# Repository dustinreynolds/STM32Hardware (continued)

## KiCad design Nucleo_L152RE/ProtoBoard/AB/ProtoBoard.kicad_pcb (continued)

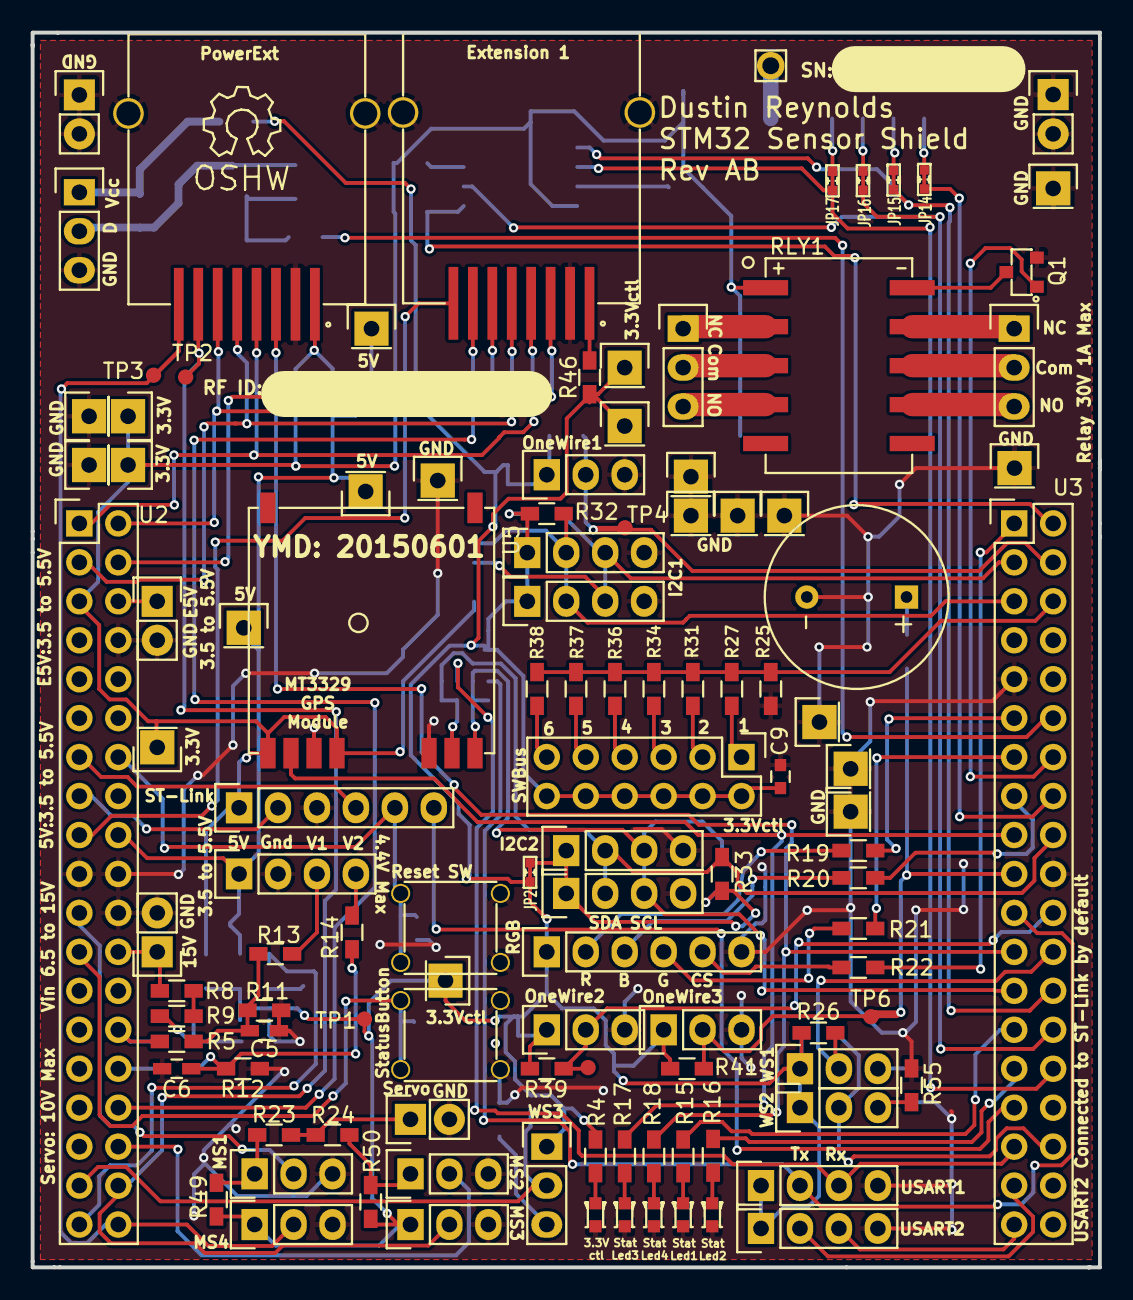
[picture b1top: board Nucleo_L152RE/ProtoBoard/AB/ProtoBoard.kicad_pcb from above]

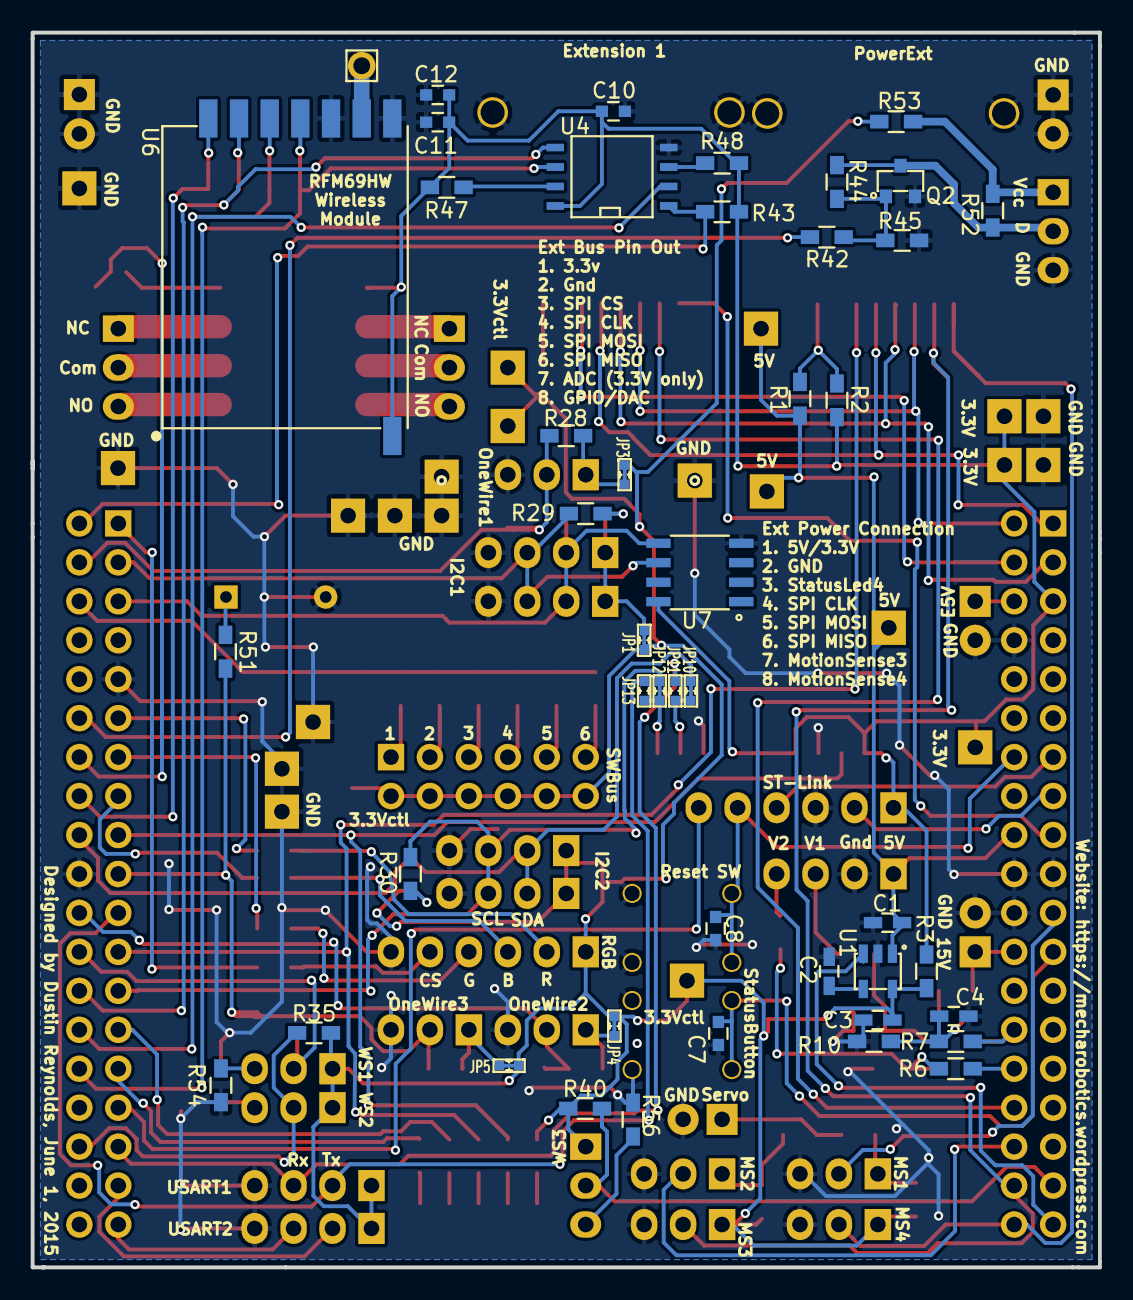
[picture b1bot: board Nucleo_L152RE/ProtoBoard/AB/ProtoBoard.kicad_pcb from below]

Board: 2 copper layers, 69.6 x 80.5 mm, 158 parts (44 on the bottom side), 98 nets.

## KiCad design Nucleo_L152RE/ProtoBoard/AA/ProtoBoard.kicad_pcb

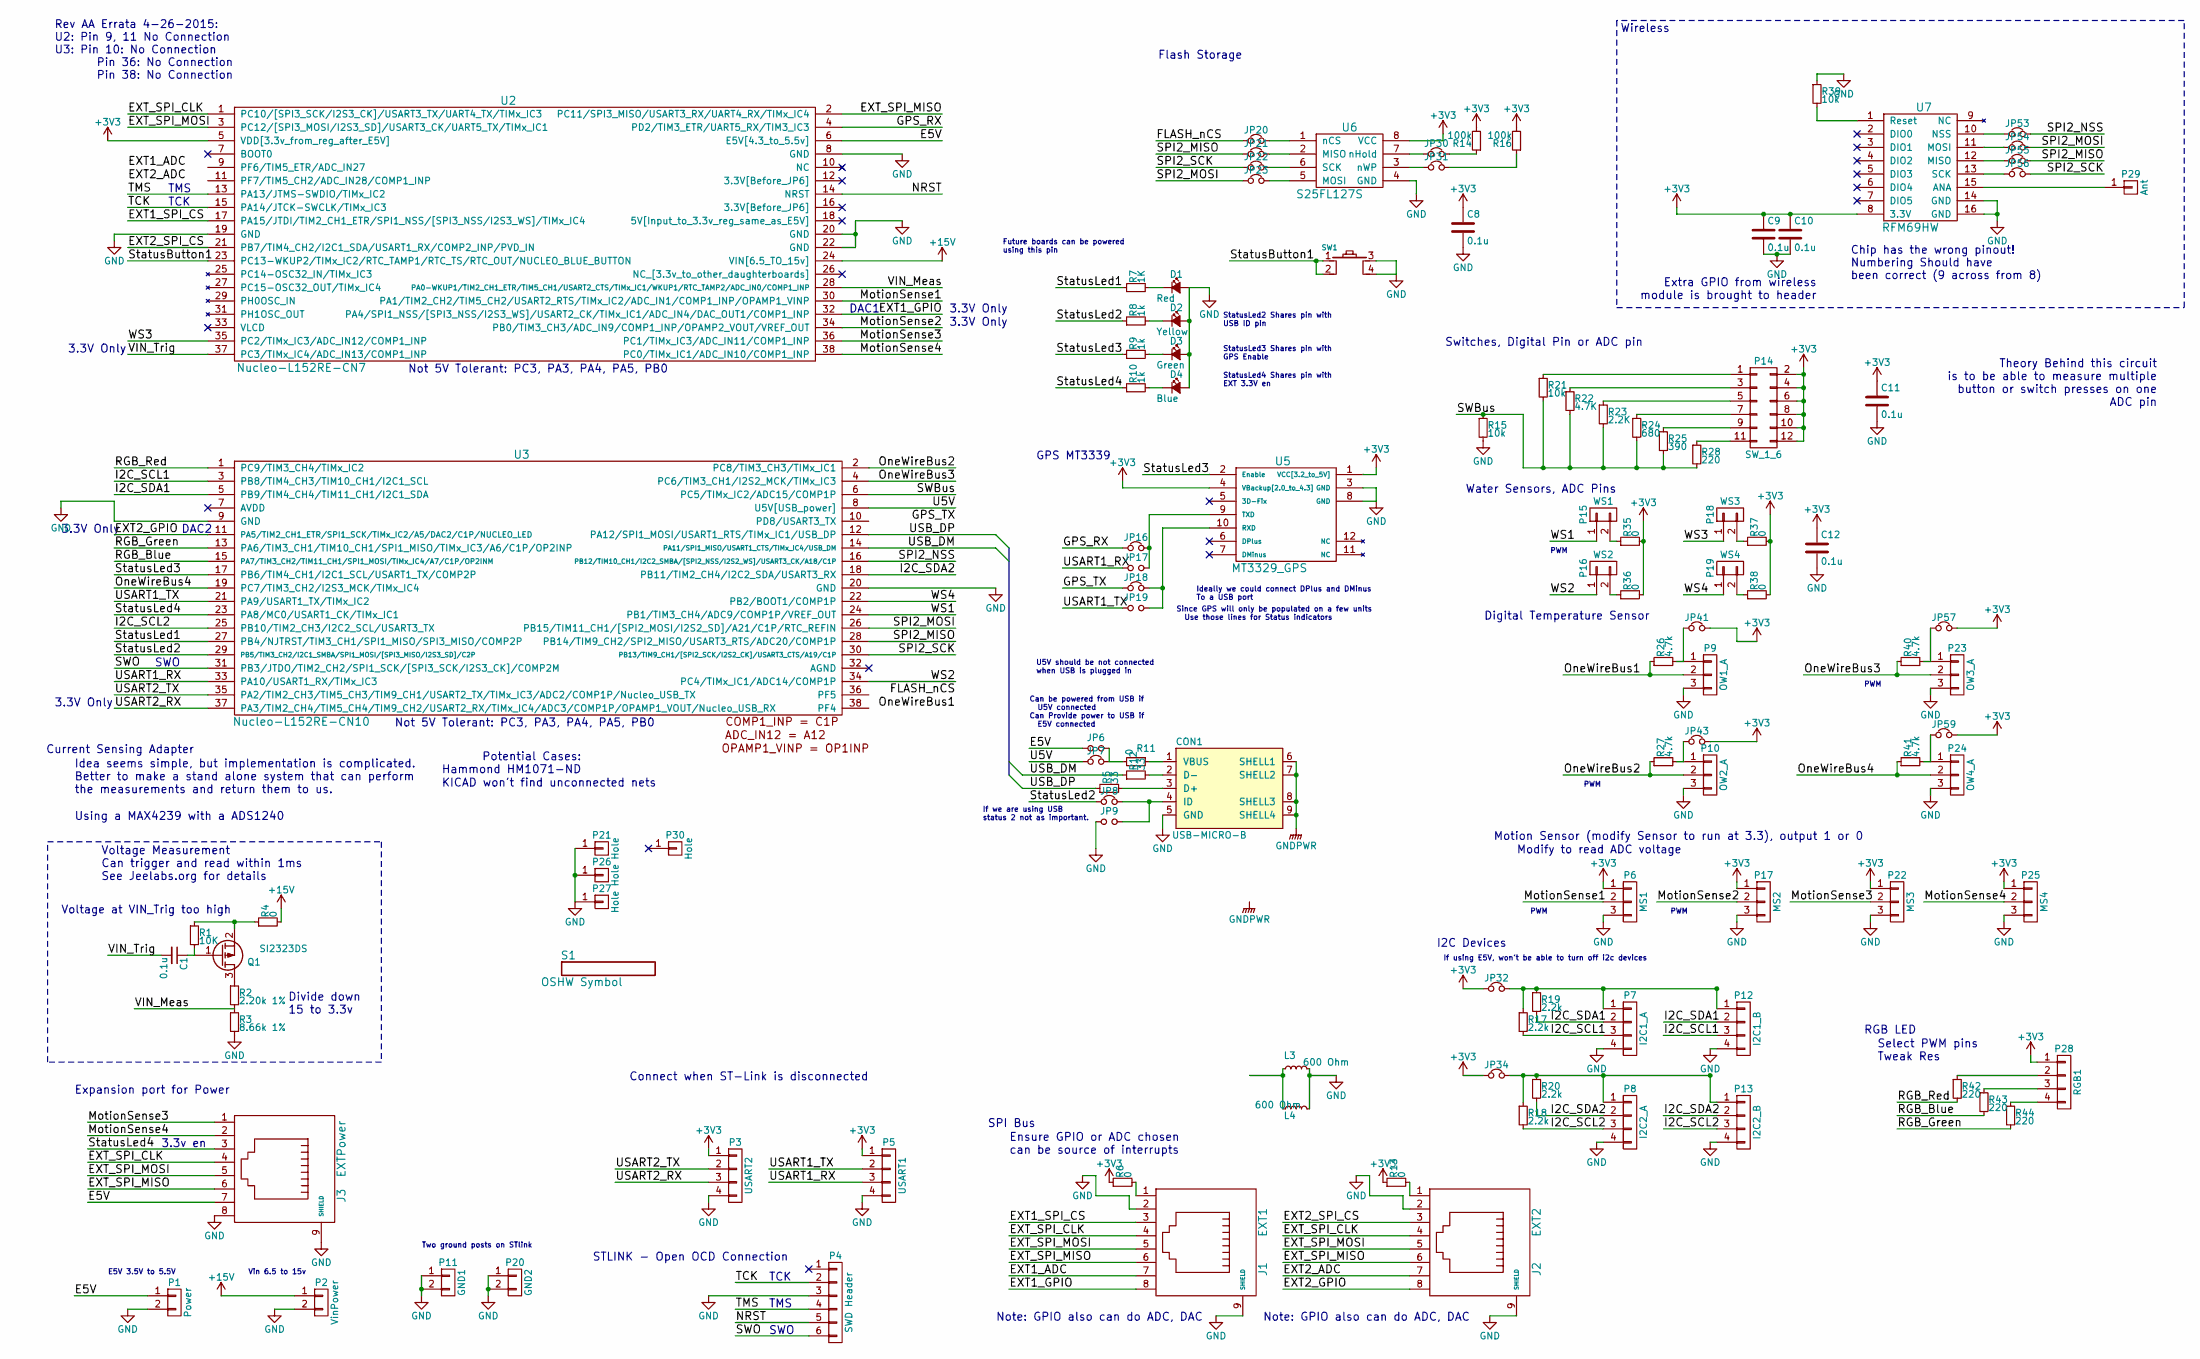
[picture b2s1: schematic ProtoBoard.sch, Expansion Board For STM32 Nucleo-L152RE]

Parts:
C1: 0.1u; C_0603_HandSoldering; Digikey Part Number 490-1532-1-ND
C8, C9, C10, C11, C12: 0.1u; C_0603; Digikey Part Number 490-1532-1-ND
CON1: USB-MICRO-B; USB_micro_AB; Digikey Part Number 609-4053-1-ND
D1: Red; LED_0603; Digikey Part Number 160-1447-1-ND
D2: Yellow; LED_0603; Digikey Part Number 160-1448-1-ND
D3: Green; LED_0603; Digikey Part Number 160-1446-1-ND
D4: Blue; LED_0603; Digikey Part Number 160-1647-1-ND
J1: EXT1; RJ45_SMD; Digikey Part Number RJLSE4238101TTR-ND
J2: EXT2; RJ45_SMD; Digikey Part Number RJLSE4238101TTR-ND
J3: EXTPower; RJ45_SMD; Digikey Part Number RJLSE4238101TTR-ND
JP6, JP9, JP17, JP19: Jumper_NO_Small; SB_NO
JP7, JP8, JP16, JP18, JP20, JP21, JP22, JP23, JP30, JP31, JP32, JP34, JP41, JP43, JP53, JP54, JP55, JP56, JP57, JP59: Jumper_NC_Small; SB_NC
L3, L4: 600 Ohm; R_0603_HandSoldering; Digikey Part Number 240-2371-1-ND
P1: Power; Pin_Header_Straight_1x02
P2: VinPower; Pin_Header_Straight_1x02
P3: USART2; Pin_Header_Straight_1x04
P4: SWD Header; Pin_Header_Straight_1x06
P5: USART1; Pin_Header_Straight_1x04
P6: MS1; Pin_Header_Straight_1x03
P7: I2C1_A; Pin_Header_Straight_1x04
P8: I2C2_A; Pin_Header_Straight_1x04
P9: OW1_A; Pin_Header_Straight_1x03
P10: OW2_A; Pin_Header_Straight_1x03
P11: GND1; Pin_Header_Straight_1x02
P12: I2C1_B; Pin_Header_Straight_1x04
P13: I2C2_B; Pin_Header_Straight_1x04
P14: SW_1_6; Pin_Header_Straight_2x06
P15: WS1; Pin_Header_Straight_1x02
P16: WS2; Pin_Header_Straight_1x02
P17: MS2; Pin_Header_Straight_1x03
P18: WS3; Pin_Header_Straight_1x02
P19: WS4; Pin_Header_Straight_1x02
P20: GND2; Pin_Header_Straight_1x02
P21, P26, P27: Hole; plat_hole_4_20
P22: MS3; Pin_Header_Straight_1x03
P23: OW3_A; Pin_Header_Straight_1x03
P24: OW4_A; Pin_Header_Straight_1x03
P25: MS4; Pin_Header_Straight_1x03
P28: RGB1; Pin_Header_Straight_1x04
P29: Ant; Pin_Header_Straight_1x01
P30: Hole; MountingHole_3mm
Q1: SI2323DS; TO-236; Digikey Part Number SI2323DS-T1-E3CT-ND
R1: 10K; R_0603_HandSoldering; Digikey Part Number P10KGCT-ND
R2: 2.20k 1%; R_0603_HandSoldering; Digikey Part Number P2.20KHCT-ND
R3: 8.66k 1%; R_0603_HandSoldering; Digikey Part Number P8.66KHCT-ND
R4, R6, R13, R35, R36, R37, R38: 0; R_0603_HandSoldering; Digikey Part Number P0.0GCT-ND
R5, R12: 33; R_0603_HandSoldering; Digikey Part Number P33HCT-ND
R7: 1K; R_0603_HandSoldering; Digikey Part Number P1.0KGCT-ND
R8, R9, R10: 1k; R_0603_HandSoldering; Digikey Part Number P1.0KGCT-ND
R11: 0; R_0603_HandSoldering; Digikey Part Number P0.0HCT-ND
R14, R16: 100k; R_0603_HandSoldering; Digikey Part Number RMCF0603FT100KTR-ND
R15, R21, R39: 10k; R_0603_HandSoldering; Digikey Part Number P10KGCT-ND
R17, R18, R19, R20: 2.2k; R_0603_HandSoldering; Digikey Part Number P2.2KGCT-ND
R22: 4.7K; R_0603_HandSoldering; Digikey Part Number P4.7KGCT-ND
R23: 2.2K; R_0603_HandSoldering; Digikey Part Number P2.2KGCT-ND
R24: 680; R_0603_HandSoldering; Digikey Part Number P680GCT-ND
R25: 390; R_0603_HandSoldering; Digikey Part Number P390GCT-ND
R26, R27, R40, R41: 4.7k; R_0603_HandSoldering; Digikey Part Number P4.7KGCT-ND
R28, R42, R43, R44: 220; R_0603_HandSoldering; Digikey Part Number P220GCT-ND
S1: OSHW Symbol; Symbol_OSHW-Logo_SilkScreen
SW1: MomentarySwitch; Tact_switch; Digikey Part Number 450-1650-ND
U2: Nucleo-L152RE-CN7; Pin_Header_Straight_2x19; Digikey Part Number 497-14363-ND
U3: Nucleo-L152RE-CN10; Pin_Header_Straight_2x19
U5: MT3329_GPS; MT3329
U6: S25FL127S; SOIC-8-FLASH; Digikey Part Number 1274-1045-ND
U7: RFM69HW

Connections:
+3V3: C8.1, C9.1, C10.1, C11.1, C12.1, JP32.1, JP34.1, JP41.2, JP43.2, JP57.2, JP59.2, P3.1, P5.1, P6.1, P14.2, P14.4, P14.6, P14.8, P14.10, P14.12, P17.1, P22.1, P25.1, P28.1, R6.1, R13.1, R14.2, R16.2, R35.2, R36.2, R37.2, R38.2, U2.5 (VDD[3.3v_from_reg_after_E5V]), U5.1 (VCC[3.2_to_5V]), U5.4 (VBackup[2.0_to_4.3]), U6.8 (VCC), U7.8 (3.3V)
+15V: P2.1, R4.2, U2.24 (VIN[6.5_TO_15v])
/E5V: J3.7, JP6.1, P1.1, U2.6 (E5V[4.3_to_5.5v])
/EXT1_ADC: J1.7, U2.9 (PF6/TIM5_ETR/ADC_IN27)
/EXT1_GPIO: J1.8, U2.32 (PA4/SPI1_NSS/[SPI3_NSS/I2S3_WS]/USART2_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)
/EXT1_SPI_CS: J1.3, U2.17 (PA15/JTDI/TIM2_CH1_ETR/SPI1_NSS/[SPI3_N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)
/EXT2_ADC: J2.7, U2.11 (PF7/TIM5_CH2/ADC_IN28/COMP1_INP)
/EXT2_GPIO: J2.8, U3.11 (PA5/TIM2_CH1_ETR/SPI1_SCK/TIMx_IC2/A5/D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)
/EXT2_SPI_CS: J2.3, U2.21 (PB7/TIM4_CH2/I2C1_SDA/USART1_RX/COMP2_I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)
/EXT_SPI_CLK: J1.4, J2.4, J3.4, U2.1 (PC10/[SPI3_SCK/I2S3_CK]/USART3_TX/UART4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)
/EXT_SPI_MISO: J1.6, J2.6, J3.6, U2.2 (PC11/SPI3_MISO/USART3_RX/UART4_RX/TIMx_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)
/EXT_SPI_MOSI: J1.5, J2.5, J3.5, U2.3 (PC12/[SPI3_MOSI/I2S3_SD]/USART3_CK/UART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)
/FLASH_nCS: JP20.1, U3.36 (PF5)
/GPS_RX: JP16.1, U2.4 (PD2/TIM3_ETR/UART5_RX/TIM3_IC3)
/GPS_TX: JP18.1, U3.10 (PD8/USART3_TX)
/I2C_SCL1: P7.3, P12.3, R17.2, U3.3 (PB8/TIM4_CH3/TIM10_CH1/I2C1_SCL)
/I2C_SCL2: P8.3, P13.3, R18.2, U3.25 (PB10/TIM2_CH3/I2C2_SCL/USART3_TX)
/I2C_SDA1: P7.2, P12.2, R19.2, U3.5 (PB9/TIM4_CH4/TIM11_CH1/I2C1_SDA)
/I2C_SDA2: P8.2, P13.2, R20.2, U3.18 (PB11/TIM2_CH4/I2C2_SDA/USART3_RX)
/MotionSense1: P6.2, U2.30 (PA1/TIM2_CH2/TIM5_CH2/USART2_RTS/TIMx_I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)
/MotionSense2: P17.2, U2.34 (PB0/TIM3_CH3/ADC_IN9/COMP1_INP/OPAMP2_V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)
/MotionSense3: J3.1, P22.2, U2.36 (PC1/TIMx_IC3/ADC_IN11/COMP1_INP)
/MotionSense4: J3.2, P25.2, U2.38 (PC0/TIMx_IC1/ADC_IN10/COMP1_INP)
/NRST: P4.5, U2.14 (NRST)
/OneWireBus1: P9.2, R26.1, U3.38 (PF4)
/OneWireBus2: P10.2, R27.1, U3.2 (PC8/TIM3_CH3/TIMx_IC1)
/OneWireBus3: P23.2, R40.1, U3.4 (PC6/TIM3_CH1/I2S2_MCK/TIMx_IC3)
/OneWireBus4: P24.2, R41.1, U3.19 (PC7/TIM3_CH2/I2S3_MCK/TIMx_IC4)
/RGB_Blue: R43.2, U3.15 (PA7/TIM3_CH2/TIM11_CH1/SPI1_MOSI/TIMx_I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)
/RGB_Green: R44.2, U3.13 (PA6/TIM3_CH1/TIM10_CH1/SPI1_MISO/TIMx_I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)
/RGB_Red: R42.2, U3.1 (PC9/TIM3_CH4/TIMx_IC2)
/SPI2_MISO: JP21.1, JP55.2, U3.28 (PB14/TIM9_CH2/SPI2_MISO/USART3_RTS/ADC2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)
/SPI2_MOSI: JP23.1, JP54.2, U3.26 (PB15/TIM11_CH1/[SPI2_MOSI/I2S2_SD]/A21/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)
/SPI2_NSS: JP53.2, U3.16 (PB12/TIM10_CH1/I2C2_SMBA/[SPI2_NSS/I2S2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)
/SPI2_SCK: JP22.1, JP56.2, U3.30 (PB13/TIM9_CH1/[SPI2_SCK/I2S2_CK]/USART3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)
/SWBus: R15.1, R21.2, R22.2, R23.2, R24.2, R25.2, R28.2, U3.6 (PC5/TIMx_IC2/ADC15/COMP1P)
/SWO: P4.6, U3.31 (PB3/JTDO/TIM2_CH2/SPI1_SCK/[SPI3_SCK/I2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)
/StatusButton1: SW1.1, SW1.2, U2.23 (PC13-WKUP2/TIMx_IC2/RTC_TAMP1/RTC_TS/RT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)
/StatusLed1: R7.1, U3.27 (PB4/NJTRST/TIM3_CH1/SPI1_MISO/SPI3_MISO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)
/StatusLed2: JP8.1, R8.1, U3.29 (PB5/TIM3_CH2/I2C1_SMBA/SPI1_MOSI/[SPI3_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)
/StatusLed3: R9.1, U3.17 (PB6/TIM4_CH1/I2C1_SCL/USART1_TX/COMP2P), U5.2 (Enable)
/StatusLed4: J3.3, R10.1, U3.23 (PA8/MC0/USART1_CK/TIMx_IC1)
/TCK: P4.2, U2.15 (PA14/JTCK-SWCLK/TIMx_IC3)
/TMS: P4.4, U2.13 (PA13/JTMS-SWDIO/TIMx_IC2)
/U5V: JP7.1, U3.8 (U5V[USB_power])
/USART1_RX: JP17.1, P5.3, U3.33 (PA10/USART1_RX/TIMx_IC3)
/USART1_TX: JP19.1, P5.2, U3.21 (PA9/USART1_TX/TIMx_IC2)
/USART2_RX: P3.3, U3.37 (PA3/TIM2_CH4/TIM5_CH4/TIM9_CH2/USART2_R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)
/USART2_TX: P3.2, U3.35 (PA2/TIM2_CH3/TIM5_CH3/TIM9_CH1/USART2_T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)
/USB_DM: R12.1, U3.14 (PA11/SPI1_MISO/USART1_CTS/TIMx_IC4/USB_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)
/USB_DP: R5.1, U3.12 (PA12/SPI1_MOSI/USART1_RTS/TIMx_IC1/USB_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)
/VIN_Meas: R2.2, R3.1, U2.28 (PA0-WKUP1/TIM2_CH1_ETR/TIM5_CH1/USART2_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)
/VIN_Trig: C1.2, U2.37 (PC3/TIMx_IC4/ADC_IN13/COMP1_INP)
/WS1: P15.1, U3.24 (PB1/TIM3_CH4/ADC9/COMP1P/VREF_OUT)
/WS2: P16.1, U3.34 (PC4/TIMx_IC1/ADC14/COMP1P)
/WS3: P18.1, U2.35 (PC2/TIMx_IC3/ADC_IN12/COMP1_INP)
/WS4: P19.1, U3.22 (PB2/BOOT1/COMP1P)
GND: C8.2, C9.2, C10.2, C11.2, C12.2, CON1.5 (GND), D1.2 (A), D2.2 (A), D3.2 (A), D4.2 (A), J1.2, J1.9 (SHIELD), J2.2, J2.9 (SHIELD), J3.8, J3.9 (SHIELD), JP9.1, L3.2, L4.2, P1.2, P2.2, P3.4, P4.3, P5.4, P6.3, P7.4, P8.4, P9.3, P10.3, P11.1, P11.2, P12.4, P13.4, P17.3, P20.1, P20.2, P21.1, P22.3, P23.3, P24.3, P25.3, P26.1, P27.1, R3.2, R15.2, R39.1, SW1.3, SW1.4, U2.8 (GND), U2.19 (GND), U2.20 (GND), U2.22 (GND), U3.9 (GND), U3.20 (GND), U5.3 (GND), U5.8 (GND), U6.4 (GND), U7.14 (GND), U7.16 (GND)
unnamed: C1.1, Q1.1 (G), R1.2
unnamed: CON1.1 (VBUS), R11.1
unnamed: CON1.2 (D-), R12.2
unnamed: CON1.3 (D+), R5.2
unnamed: CON1.4 (ID), JP8.2, JP9.2
unnamed: D1.1 (K), R7.2
unnamed: D2.1 (K), R8.2
unnamed: D3.1 (K), R9.2
unnamed: D4.1 (K), R10.2
unnamed: J1.1, R6.2
unnamed: J2.1, R13.2
unnamed: JP6.2, JP7.2, R11.2
unnamed: JP16.2, JP17.2, U5.9 (TXD)
unnamed: JP18.2, JP19.2, U5.10 (RXD)
unnamed: JP20.2, U6.1 (nCS)
unnamed: JP21.2, U6.2 (MISO)
unnamed: JP22.2, U6.6 (SCK)
unnamed: JP23.2, U6.5 (MOSI)
unnamed: JP30.1, U6.7 (nHold)
unnamed: JP30.2, R14.1
unnamed: JP31.1, U6.3 (nWP)
unnamed: JP31.2, R16.1
unnamed: JP32.2, P7.1, P12.1, R17.1, R19.1
unnamed: JP34.2, P8.1, P13.1, R18.1, R20.1
unnamed: JP41.1, P9.1, R26.2
unnamed: JP43.1, P10.1, R27.2
unnamed: JP53.1, U7.10 (NSS)
unnamed: JP54.1, U7.11 (MOSI)
unnamed: JP55.1, U7.12 (MISO)
unnamed: JP56.1, U7.13 (SCK)
unnamed: JP57.1, P23.1, R40.2
unnamed: JP59.1, P24.1, R41.2
unnamed: P14.1, R21.1
unnamed: P14.3, R22.1
unnamed: P14.5, R23.1
unnamed: P14.7, R24.1
unnamed: P14.9, R25.1
unnamed: P14.11, R28.1
unnamed: P15.2, R35.1
unnamed: P16.2, R36.1
unnamed: P18.2, R37.1
unnamed: P19.2, R38.1
unnamed: P28.2, R42.1
unnamed: P28.3, R43.1
unnamed: P28.4, R44.1
unnamed: P29.1, U7.15 (ANA)
unnamed: Q1.2 (S), R1.1, R4.1
unnamed: Q1.3 (D), R2.1
unnamed: R39.2, U7.1 (Reset)

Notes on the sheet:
TCK
TMS
SWO
Wireless
Connect when ST-Link is disconnected
Not 5V Tolerant: PC3, PA3, PA4, PA5, PB0
Switches, Digital Pin or ADC pin
Water Sensors, ADC Pins
Digital Temperature Sensor
Motion Sensor (modify Sensor to run at 3.3), output 1 or 0
Current Sensing Adapter
STLINK - Open OCD Connection
Theory Behind this circuit is to be able to measure multiple button or switch presses on one ADC pin
Flash Storage
Idea seems simple, but implementation is complicated. Better to make a stand alone system that can perform the measurements and return them to us.
Using a MAX4239 with a ADS1240
If using E5V, won't be able to turn off i2c devices
Extra GPIO from wireless module is brought to header
Potential Cases: Hammond HM1071-ND
SPI Bus
Ensure GPIO or ADC chosen can be source of interrupts
RGB LED
Select PWM pins Tweak Res
Voltage Measurement Can trigger and read within 1ms See Jeelabs.org for details
Divide down 15 to 3.3v
DAC2
DAC1
Note: GPIO also can do ADC, DAC
U5V should be not connected when USB is plugged in
Ideally we could connect DPlus and DMinus To a USB port
Vin 6.5 to 15v
E5V 3.5V to 5.5V
If we are using USB status 2 not as important.
I2C Devices
StatusLed2 Shares pin with USB ID pin
Can be powered from USB if U5V connected Can Provide power to USB if E5V connected
PWM
GPS MT3339
Future boards can be powered using this pin
Since GPS will only be populated on a few units Use those lines for Status indicators

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
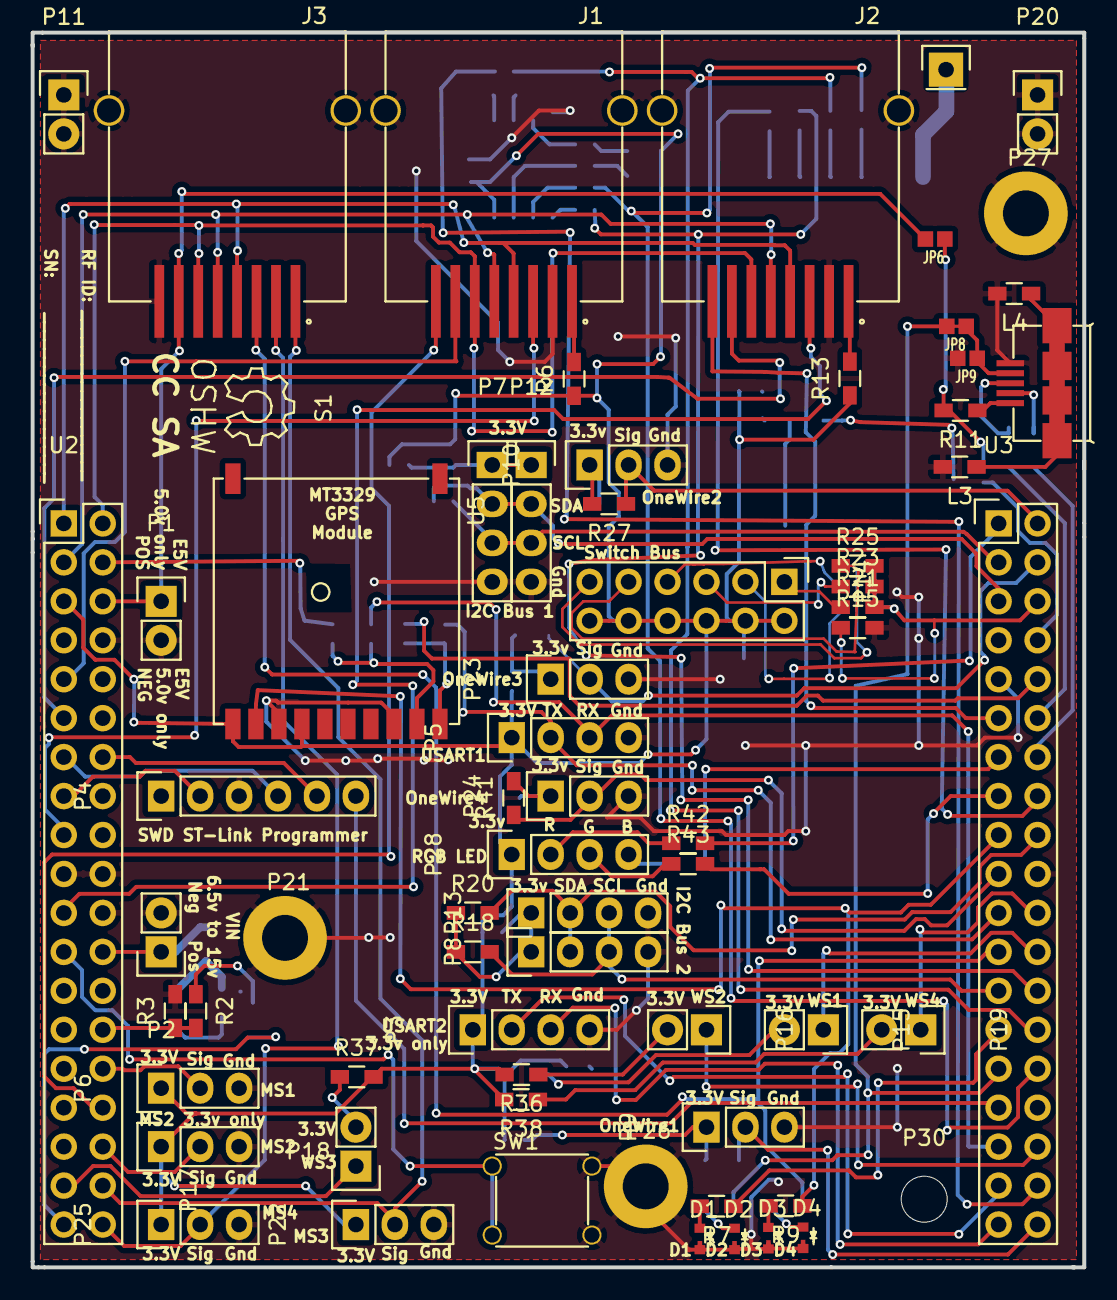
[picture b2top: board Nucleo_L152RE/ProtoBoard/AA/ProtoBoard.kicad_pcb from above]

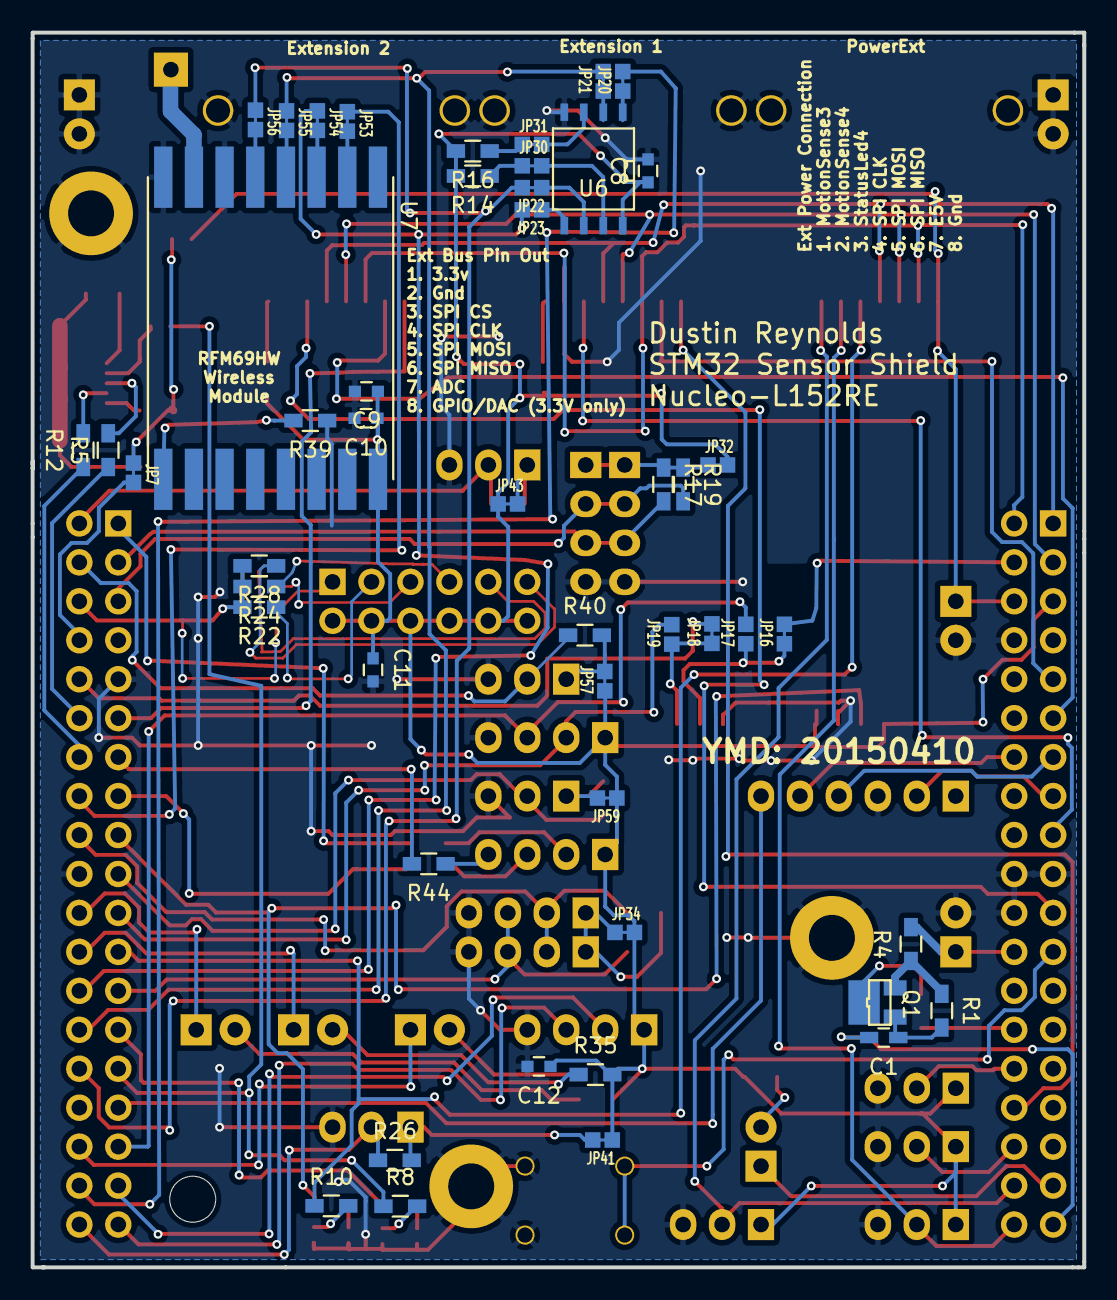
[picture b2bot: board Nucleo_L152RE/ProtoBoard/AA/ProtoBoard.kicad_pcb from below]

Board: 2 copper layers, 68.6 x 80.5 mm, 116 parts (48 on the bottom side), 108 nets.

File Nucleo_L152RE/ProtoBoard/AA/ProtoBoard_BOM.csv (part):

"Source:","C:/Customers/Dustin/SensorNodes/STM32/EE/Nucleo_L152RE/ProtoBoard/AA/ProtoBoard.sch"
"Date:","4/10/2015 3:52:45 PM"
"Tool:","Eeschema (2015-03-26 BZR 5542)-product"
"Generator:","dustin_bom_csv_grouped_by_value_with_fp.py"
"Component Count:","116"
"Ref","Quantity","Value","Cmp name","Footprint","Description","Vendor","Datasheet","Digikey Part Number","Digikey URL","Mouser Part Number","Mouser URL","Ebay","Manufacture Part Number"
"C1, ","1","0.1u","C_Small","Capacitors_SMD:C_0603_HandSoldering","Unpolarized capacitor","","http://www.digikey.com/product-detail/en/GRM188R71C104KA01D/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","490-1532-1-ND","","","","","GRM188R71C104KA01D"
"C10, C9, C8, C11, C12, ","5","0.1u","C","Capacitors_SMD:C_0603","Unpolarized capacitor","","","490-1532-1-ND","","","","","GRM188R71C104KA01D"
"CON1, ","1","USB-MICRO-B","USB-MICRO-B","nucleo:USB_micro_AB","USB Mini B connector","","http://www.digikey.com/product-detail/en/10104111-0001LF/609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","609-4053-1-ND","http://www.digikey.com/product-detail/en/10104111-0001LF/609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","","","","10104111-0001LF"
"D1, ","1","Red","Led_Small","nucleo:LED_0603","Led","","http://optoelectronics.liteon.com/upload/download/DS22-2000-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","160-1447-1-ND","http://www.digikey.com/product-detail/en/LTST-C191KRKT/160-1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","","","","LTST-C191KRKT"
"D2, ","1","Yellow","Led_Small","nucleo:LED_0603","Led","","http://optoelectronics.liteon.com/upload/download/DS22-2000-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","160-1448-1-ND","http://www.digikey.com/product-detail/en/LTST-C191KSKT/160-1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","","","","LTST-C191KSKT"
"D3, ","1","Green","Led_Small","nucleo:LED_0603","Led","","http://optoelectronics.liteon.com/upload/download/DS22-2000-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","160-1446-1-ND","http://www.digikey.com/product-detail/en/LTST-C191KGKT/160-1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","","","","LTST-C191KGKT"
"D4, ","1","Blue","Led_Small","nucleo:LED_0603","Led","","http://optoelectronics.liteon.com/upload/download/DS22-2000-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","160-1647-1-ND","http://www.digikey.com/product-detail/en/LTST-C191TBKT/160-1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","","","","LTST-C191TBKT"
"J1, ","1","EXT1","RJ45","nucleo:RJ45_SMD","","","http://www.digikey.com/product-detail/en/RJLSE4238101T/RJLSE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","RJLSE4238101TTR-ND","http://www.digikey.com/product-detail/en/RJLSE4238101T/RJLSE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","","","","RJLSE4238101T"
"J2, ","1","EXT2","RJ45","nucleo:RJ45_SMD","","","http://www.digikey.com/product-detail/en/RJLSE4238101T/RJLSE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","RJLSE4238101TTR-ND","http://www.digikey.com/product-detail/en/RJLSE4238101T/RJLSE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","","","","RJLSE4238101T"
"J3, ","1","EXTPower","RJ45","nucleo:RJ45_SMD","","","http://www.digikey.com/product-detail/en/RJLSE4238101T/RJLSE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","RJLSE4238101TTR-ND","http://www.digikey.com/product-detail/en/RJLSE4238101T/RJLSE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","","","","RJLSE4238101T"
"JP19, JP17, JP9, JP6, ","4","Jumper_NO_Small","Jumper_NO_Small","nucleo:SB_NO","Jumper normally open","","","","","","","",""
"JP53, JP54, JP55, JP56, JP20, JP21, JP22, JP23, JP30, JP31, JP16, JP18, JP8, JP34, JP32, JP7, JP41, JP57, JP59, JP43, ","20","Jumper_NC_Small","Jumper_NC_Small","nucleo:SB_NC","Jumper normally close","","","","","","","",""
"L4, L3, ","2","600 Ohm","L_Small","Resistors_SMD:R_0603_HandSoldering","Inductor","","http://www.digikey.com/product-detail/en/MI0603J601R-10/240-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","240-2371-1-ND","http://www.digikey.com/product-detail/en/MI0603J601R-10/240-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","","","","MI0603J601R-10"
"P1, ","1","Power","CONN_01X02","Pin_Headers:Pin_Header_Straight_1x02","","","","","","","","",""
"P10, ","1","OW2_A","CONN_01X03","Pin_Headers:Pin_Header_Straight_1x03","","","","","","","","",""
"P11, ","1","GND1","CONN_01X02","Pin_Headers:Pin_Header_Straight_1x02","","","","","","","","",""
"P12, ","1","I2C1_B","CONN_01X04","Pin_Headers:Pin_Header_Straight_1x04","","","","","","","","",""
"P13, ","1","I2C2_B","CONN_01X04","Pin_Headers:Pin_Header_Straight_1x04","","","","","","","","",""
"P14, ","1","SW_1_6","CONN_02X06","Pin_Headers:Pin_Header_Straight_2x06","","","","","","","","",""
"P15, ","1","WS1","CONN_01X02","Pin_Headers:Pin_Header_Straight_1x02","","","","","","","","",""
"P16, ","1","WS2","CONN_01X02","Pin_Headers:Pin_Header_Straight_1x02","","","","","","","","",""
"P17, ","1","MS2","CONN_01X03","Pin_Headers:Pin_Header_Straight_1x03","","","","","","","","",""
"P18, ","1","WS3","CONN_01X02","Pin_Headers:Pin_Header_Straight_1x02","","","","","","","","",""
"P19, ","1","WS4","CONN_01X02","Pin_Headers:Pin_Header_Straight_1x02","","","","","","","","",""
"P2, ","1","VinPower","CONN_01X02","Pin_Headers:Pin_Header_Straight_1x02","","","","","","","","",""
"P20, ","1","GND2","CONN_01X02","Pin_Headers:Pin_Header_Straight_1x02","","","","","","","","",""
"P21, P26, P27, ","3","Hole","CONN_01X01","nucleo:plat_hole_4_20","","","","","","","","",""
"P22, ","1","MS3","CONN_01X03","Pin_Headers:Pin_Header_Straight_1x03","","","","","","","","",""
"P23, ","1","OW3_A","CONN_01X03","Pin_Headers:Pin_Header_Straight_1x03","","","","","","","","",""
"P24, ","1","OW4_A","CONN_01X03","Pin_Headers:Pin_Header_Straight_1x03","","","","","","","","",""
"P25, ","1","MS4","CONN_01X03","Pin_Headers:Pin_Header_Straight_1x03","","","","","","","","",""
"P28, ","1","RGB1","CONN_01X04","Pin_Headers:Pin_Header_Straight_1x04","","","","","","","","",""
"P29, ","1","Ant","CONN_01X01","Pin_Headers:Pin_Header_Straight_1x01","","","","","","","","",""
"P3, ","1","USART2","CONN_01X04","Pin_Headers:Pin_Header_Straight_1x04","","","","","","","","",""
"P30, ","1","Hole","CONN_01X01","Mounting_Holes:MountingHole_3mm","","","","","","","","",""
"P4, ","1","SWD Header","CONN_01X06","Pin_Headers:Pin_Header_Straight_1x06","","","","","","","","",""
"P5, ","1","USART1","CONN_01X04","Pin_Headers:Pin_Header_Straight_1x04","","","","","","","","",""
"P6, ","1","MS1","CONN_01X03","Pin_Headers:Pin_Header_Straight_1x03","","","","","","","","",""
"P7, ","1","I2C1_A","CONN_01X04","Pin_Headers:Pin_Header_Straight_1x04","","","","","","","","",""
"P8, ","1","I2C2_A","CONN_01X04","Pin_Headers:Pin_Header_Straight_1x04","","","","","","","","",""
"P9, ","1","OW1_A","CONN_01X03","Pin_Headers:Pin_Header_Straight_1x03","","","","","","","","",""
"Q1, ","1","SI2323DS","Q_PMOS_GSD","nucleo:TO-236","Transistor P-MOSFET (general)","","http://www.vishay.com/docs/72024/72024.pdf","SI2323DS-T1-E3CT-ND","","","","","SI2323DS-T1-E3"
"R1, ","1","10K","R_Small","Resistors_SMD:R_0603_HandSoldering","Resistor","","","P10KGCT-ND","http://www.digikey.com/product-detail/en/ERJ-3GEYJ103V/P10KG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","","","","ERJ-3GEYJ103V"
"R14, R16, ","2","100k","R_Small","Resistors_SMD:R_0603_HandSoldering","Resistor","","","RMCF0603FT100KTR-ND","http://www.digikey.com/product-detail/en/RMCF0603FT100K/RMCF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","","","","CRCW0603100KFKEA"
"R2, ","1","2.20k 1%","R_Small","Resistors_SMD:R_0603_HandSoldering","Resistor","","","P2.20KHCT-ND","","","","","ERJ-3EKF2201V"
"R20, R18, R17, R19, ","4","2.2k","R_Small","Resistors_SMD:R_0603_HandSoldering","Resistor","","","P2.2KGCT-ND","","","","","ERJ-3GEYJ222V"
"R21, R15, R39, ","3","10k","R_Small","Resistors_SMD:R_0603_HandSoldering","Resistor","","","P10KGCT-ND","http://www.digikey.com/product-detail/en/ERJ-3GEYJ103V/P10KG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","","","","ERJ-3GEYJ103V"
"R22, ","1","4.7K","R_Small","Resistors_SMD:R_0603_HandSoldering","Resistor","","","P4.7KGCT-ND","http://www.digikey.com/product-detail/en/ERJ-3GEYJ472V/P4.7K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","","","","ERJ-3GEYJ472V"
"R23, ","1","2.2K","R_Small","Resistors_SMD:R_0603_HandSoldering","Resistor","","","P2.2KGCT-ND","","","","","ERJ-3GEYJ222V"
"R24, ","1","680","R_Small","Resistors_SMD:R_0603_HandSoldering","Resistor","","","P680GCT-ND","","","","","CRCW0603680RFKEA"
"R25, ","1","390","R_Small","Resistors_SMD:R_0603_HandSoldering","Resistor","","","P390GCT-ND","","","","","ERJ-3GEYJ390V"
"R26, R27, R40, R41, ","4","4.7k","R_Small","Resistors_SMD:R_0603_HandSoldering","Resistor","","","P4.7KGCT-ND","","","","","ERJ-3GEYJ472V"
"R28, R42, R43, R44, ","4","220","R_Small","Resistors_SMD:R_0603_HandSoldering","Resistor","","","P220GCT-ND","","","","","ERJ-3GEYJ222V"
"R3, ","1","8.66k 1%","R_Small","Resistors_SMD:R_0603_HandSoldering","Resistor","","","P8.66KHCT-ND","","","","","ERJ-3EKF8661V"
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
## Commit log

2015-03-29 Initial commit, board passed DRC
2015-03-30 Have more of the components layout and specified.
2015-03-31 Have all footprints selected for components, now starting to organize parts on board.
2015-04-01 Removed many jumper bridges, starting to get a feel for how many components there will be and where they will be.
2015-04-02 Saving initial schematic. I plan on removing power regulators to make the board simpler to design and layout. Voltage regulation can happen off board.
2015-04-03 About to remove a few extra connectors.
2015-04-03 all remaining components fit on one board.
2015-04-04 performing more routing of the board. This board is quickly becoming complicated with all of the headers to navigate around.
2015-04-04 All signals routed, now the only remaining thing is ground signals and/or ground planes.
2015-04-04 All pads now connected.
2015-04-05 About to modify Solder Bridges to be a smaller 0402 package rather than the custom one which generates DRC errors.
2015-04-05 In process of checking all footprints. Found mistake in usb micro AB footprint.
2015-04-05 Fixed Flash and Pmos footprints. Added symbol part for schematic.
2015-04-05 Commit just before implementing groundplanes.
2015-04-05 Ground plane implemented on 2 layers.
2015-04-05 Adding licensing to Pcbnew.
2015-04-06 Testing inserting metadata into schematics about parts used for BOM generation.
2015-04-06 Adding part details to schematic, creating BOM tools.
2015-04-07 Updated schematic with links to almost all parts.
2015-04-07 Adding BOM and final schematics.
2015-04-08 Ordered parts from Mouser for Protoboard AA.
2015-04-10 Submitted first printing of AA version. Uploading Gerbers since we would like to be able to get back to this point.
2015-04-10 Removing extra file.
2015-04-10 Moved entire repository to another folder to test the ability to load libraries, schematics, pcb. Success.
2015-04-10 Adding Readme
    Adding Readme
2015-04-10 Adding descriptions for the general repository and specifically for the Nucleo_L152RE/ProtoBoard hardware release.
2015-04-10 Adjusting link to point to the develop branch (which is pretty empty)
2015-04-11 Changing some documentation on schematic's.
2015-04-11 Add PDF schematics.
2015-04-27 Found 5 unconnected pins on Nucleo L152RE, so I've added an Errata and deleted the wires for the effected nets.
2015-05-12 Adding notes to schematic and board layout to indicate the very broken wireless module interface. New board will need to be created to fix the issue.
2015-05-18 Making more changes on Rev AB. Found that the voltage measurement circuit didn't work as expected, so it has been replaced with a voltage divider. Removing second Ethernet port since they take up a l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
2015-05-23 Split schematic into multiple pages. Added servo power input and calculated voltage dividers for ADC measurements with capacitors so that the measurements can be read by the ADC.
2015-05-23 Adding datasheet for LDS3985 3.3V LDO regulator
2015-05-27 Components mostly laid out into final resting positions with exception of plethora of single pin connections for easily connecting to GND, 3.3V, 5V, 3.3Vctl.
2015-05-28 One of the connectors is routed, now to do the other one.
2015-05-29 Added many traces which will have to be removed since I put via's on pads :/
2015-05-31 Final draft with all traces and artwork in place.
2015-06-02 Finished AB board.
2015-06-02 Adding datasheets.
2015-06-03 Updated MFG part numbers on schematic for BOM generation.
